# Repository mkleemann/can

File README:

AVR module: CAN - using MCP2515 and MCP2551
================================================================================

A submodule used in other projects. Currently cmake is used to build a library
of the module. The path structure within the project should be as follows.
The includes are looked for in the subdirectory "config", "spi" and "util" at
the same level as the module.

Environment:
------------

<some project path>
:
|
+- config
|  |
|  +- can_config_mcp2515.c
|  +- can_config_mcp2515.h
|  +- spi_config.h
|
+- can
|  |
|  +- <submodule sources>
|
+- spi
|  |
|  +- <submodule sources>
|
+- util
   |
   +- <submodule util files>

Use the following git commands to get the submodule:

# to get the submodule
git submodule add git@github.com:mkleemann/can.git <path/to/can/module>
# commit the submodule to your repository
git commit

# update your submodule, when needs be
git submodule update

To use the submodule, you may make use of the cmake-avr toolchain. The
project has to define the include search path at the parent directory
of the module.

Have fun!

M.

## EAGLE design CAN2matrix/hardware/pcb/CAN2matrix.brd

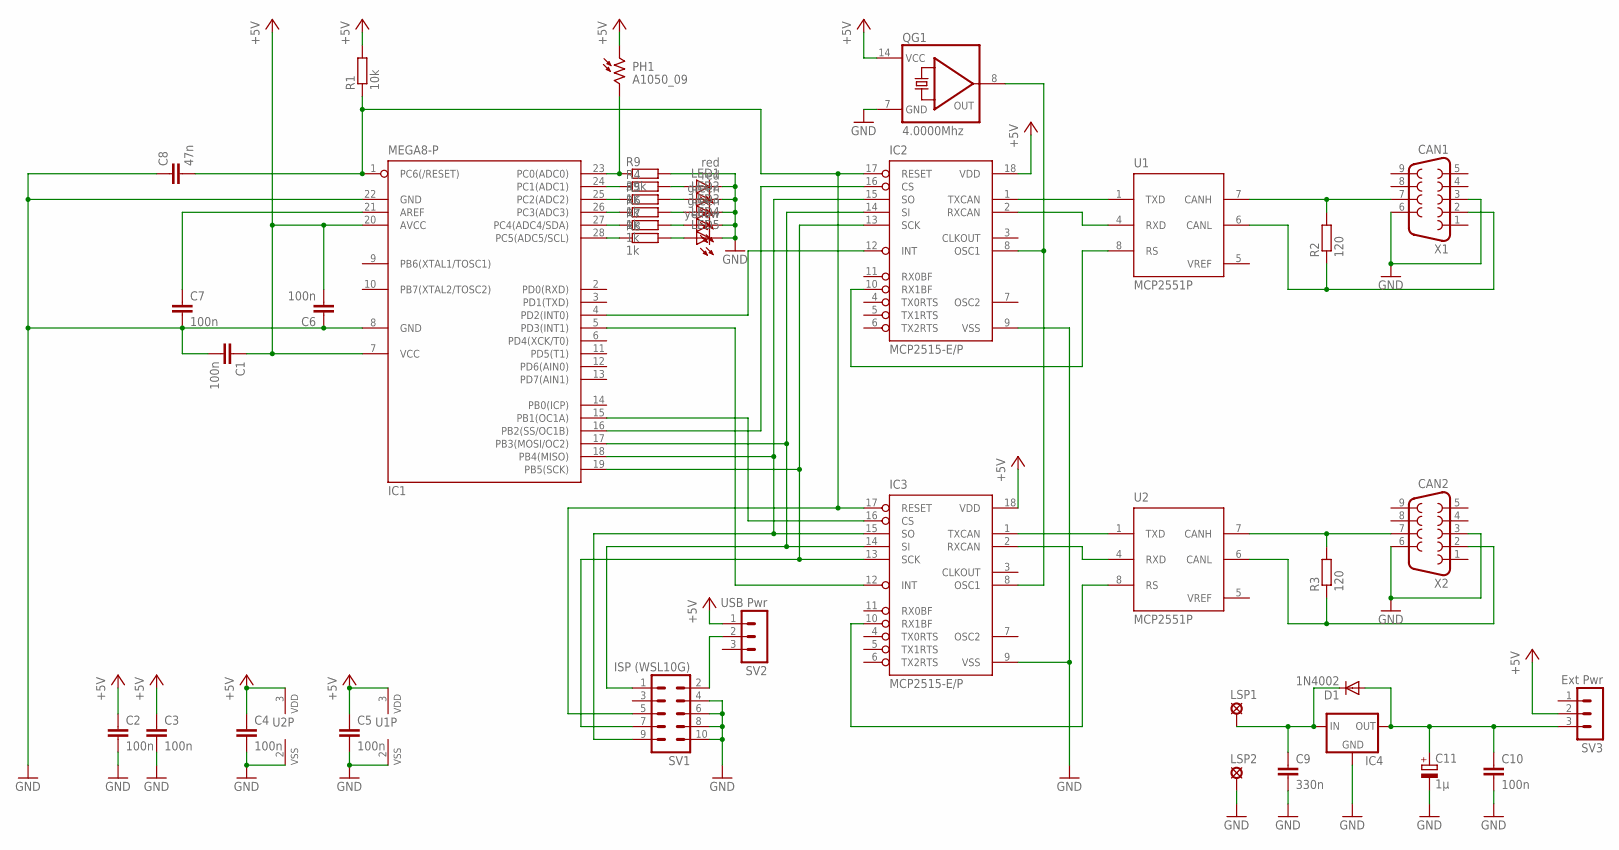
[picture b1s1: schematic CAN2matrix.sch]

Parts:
C1, C2, C3, C4, C5, C6, C7, C10: 100n; C050-025X075
C8: 47n; C050-025X075
C9: 330n; C050-025X075
C11: 1µ; E2,5-7
D1: 1N4002; DO41-10
IC1: MEGA8-P; DIL28-3
IC2, IC3: MCP2515-E/P; DIL18
IC4: 78LXX
LED1, LED2: red; LED3MM
LED3, LED4: green; LED3MM
LED5: yellow; LED3MM
LSP1: +12V; SE14
LSP2: SE14
PH1: A1050_09; T0-46-A10XX
QG1: 4.0000Mhz; DIL14S
R1: 10k; 0207/2V
R2, R3: 120; 0207/2V
R4, R5, R6, R7, R8: 1k; 0207/10
R9: 39k; 0204/7
SV1: ISP (WSL10G); ML10
SV2: USB Pwr; MA03-1
SV3: Ext Pwr; MA03-1
U1, U2: MCP2551P; DIL8
X1: CAN1; F09HP
X2: CAN2; F09HP

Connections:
+5V: C1.1, C2.1, C3.1, C4.1, C5.1, C6.2, IC1.7 (VCC), IC1.20 (AVCC), IC2.18 (VDD), IC3.18 (VDD), PH1.1, QG1.14 (VCC), R1.2, SV2.1, SV3.2, U1.3 (VDD), U2.3 (VDD)
+12V: C9.1, D1.C, IC4.IN, LSP1.MP
GND: C1.2, C2.2, C3.2, C4.2, C5.2, C6.1, C7.2, C8.1, C9.2, C10.2, C11.-, IC1.8 (GND), IC1.22 (GND), IC2.9 (VSS), IC3.9 (VSS), IC4.GND, LED1.K (C), LED2.K (C), LED3.K (C), LED4.K (C), LED5.K (C), LSP2.MP, QG1.7 (GND), R9.2, SV1.4, SV1.6, SV1.8, SV1.10, U1.2 (VSS), U2.2 (VSS), X1.3, X1.6, X2.3, X2.6
unnamed: IC1.18 (PB4(MISO)), IC2.15 (SO), IC3.15 (SO), SV1.9
unnamed: IC1.17 (PB3(MOSI/OC2)), IC2.14 (SI), IC3.14 (SI), SV1.1
unnamed: IC1.19 (PB5(SCK)), IC2.13 (SCK), IC3.13 (SCK), SV1.7
unnamed: R2.2, U1.7 (CANH), X1.7
unnamed: R3.2, U2.7 (CANH), X2.7
unnamed: R3.1, U2.6 (CANL), X2.2
unnamed: IC3.10 (RX1BF), U2.8 (RS)
unnamed: C7.1, IC1.21 (AREF)
unnamed: C8.2, IC1.1 (PC6(/RESET)), IC2.17 (RESET), IC3.17 (RESET), R1.1, SV1.5
unnamed: IC2.1 (TXCAN), U1.1 (TXD)
unnamed: IC2.2 (RXCAN), U1.4 (RXD)
unnamed: IC3.1 (TXCAN), U2.1 (TXD)
unnamed: IC3.2 (RXCAN), U2.4 (RXD)
unnamed: IC1.16 (PB2(SS/OC1B)), IC2.16 (CS)
unnamed: IC1.15 (PB1(OC1A)), IC3.16 (CS)
unnamed: IC1.4 (PD2(INT0)), IC2.12 (INT)
unnamed: IC1.5 (PD3(INT1)), IC3.12 (INT)
unnamed: IC2.8 (OSC1), IC3.8 (OSC1), QG1.8 (OUT)
unnamed: IC2.10 (RX1BF), U1.8 (RS)
unnamed: R2.1, U1.6 (CANL), X1.2
unnamed: SV1.2, SV2.2
unnamed: IC1.24 (PC1(ADC1)), R4.1
unnamed: IC1.25 (PC2(ADC2)), R5.1
unnamed: IC1.26 (PC3(ADC3)), R6.1
unnamed: IC1.27 (PC4(ADC4/SDA)), R7.1
unnamed: IC1.28 (PC5(ADC5/SCL)), R8.1
unnamed: LED1.A, R4.2
unnamed: LED2.A, R5.2
unnamed: LED3.A, R6.2
unnamed: LED4.A, R7.2
unnamed: LED5.A, R8.2
unnamed: IC1.23 (PC0(ADC0)), PH1.2, R9.1
unnamed: C10.1, C11.+, D1.A, IC4.OUT, SV3.3
VREF: U1.5 (VREF), U2.5 (VREF)

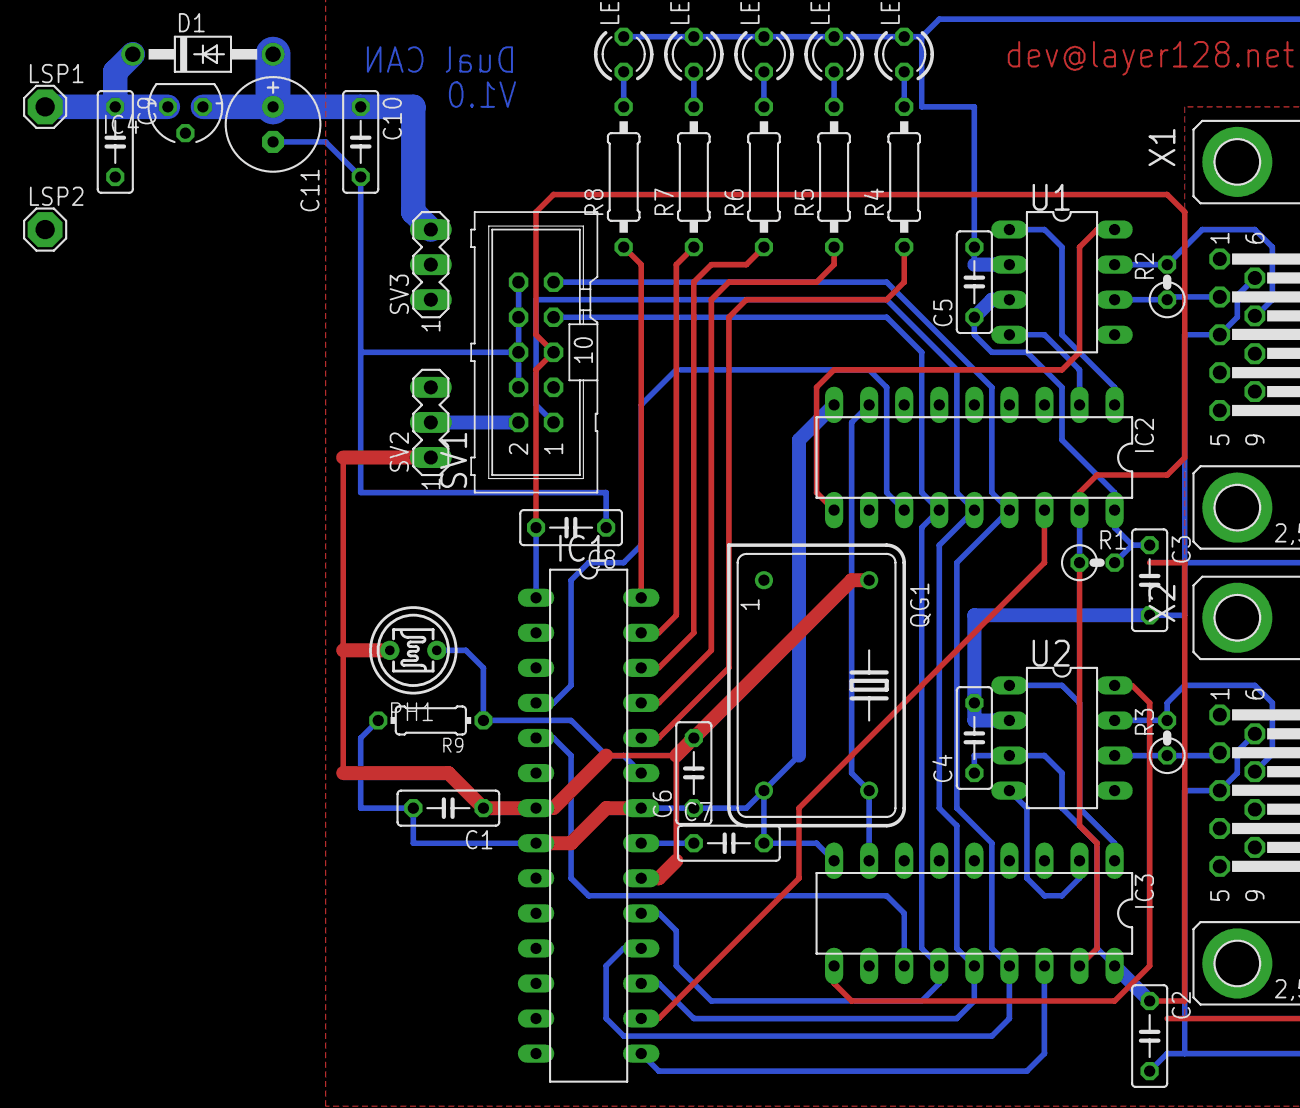
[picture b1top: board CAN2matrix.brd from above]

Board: 2 copper layers, 41 parts (0 on the bottom side), 37 nets.

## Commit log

2011-12-02 initial version
2011-12-02 add code to spi and uart, remove eeprom, change Release options
2011-12-04 Defintion of utilities for PORT/PIN usage and debug prints.
2011-12-06 implement first version of led control
2011-12-06 make it compilable
2011-12-13 intermediate stage with tested LEDs on ATmega8
2011-12-13 remove file can.h
2011-12-16 put #define of number of leds to enum
2011-12-16 last changes to UART for testing with MAX232
2011-12-16 change documentation wthin file
2011-12-16 intermediate stage for CAN implementation - compiles; not yet tested
2011-12-17 add F_CPU and MCP_CLOCK to compiler symbols to avoid delay.h warnings
2011-12-17 CAN init w/o filters; compiles; not tested
2011-12-17 rename can_write to can_send
2011-12-17 setup SPI port pins
2011-12-17 intermediate stage for CAN cluster; acknowledgements; compiles; not tested
2011-12-19 intermediate stage for CAN cluster - send/receive; compiles; not tested
2011-12-19 changed AVRStudio project files
2011-12-19 add modes of operation to MCP2515 control; compiles; not tested
2011-12-20 guard SPI pins and beautify code a little
2011-12-21 major bugs in macros fixed
2011-12-21 use different macros and pin definitions to avoid bugs
2011-12-21 intermediate stage with new approach to CS/INT pins; partly simulated; compiles; not tested on HW
2011-12-21 testing with one CAN chip attached; intermediate stage
2011-12-21 update AVRStudio 5 project files
2011-12-21 update AVRStudio 5 project files - change back to atmega8 (from 16)
2011-12-26 add filters to CAN init; some changes to can_get_message (skip ext ids); minor changes; first tested with live CAN - OK
2011-12-26 minor changes to SPI files
2011-12-26 bug fixed/newly added utilities
2011-12-26 test program with one attached MCP2515; working with external CAN adapter
2011-12-26 changed project files for AVRStudio 5
2011-12-27 add README file to project
2011-12-27 add AVRStudio 5 note to README
2011-12-27 add LICENSE (beerware) and update README
2011-12-27 add ANY BEVERAGE-WARE license to files
2011-12-27 add hardware/schematics for documentation; schematics also as EAGLE V6.0 file
2011-12-27 move sleep/wakeup functions to can_sleep_mcp2515.c
2011-12-27 enable Wake On CAN interrupt in configuration; introduce different wake up scenarios for sleep mode; compiles; not tested
2011-12-27 update README (typo)
2011-12-27 update schematics to provide possibility to disconnect ISP power supply from board
2011-12-27 move clear filter function to can_filter_mcp2515.c
2011-12-29 add filter setup functions (no implementation); cleanup a little
2011-12-29 implement Timer0 simple use for overflow interrupt; Timer1/2 still not implemented
2011-12-29 use Timer0 to trigger simple CAN msg every 250ms (approx.); verified and tested
2011-12-29 update AVRStudio 5 files
2011-12-29 add start/stop functions for Timer0; init stops timer
2011-12-29 set RX1BF as digital output to use as sleep mode indicator for MCP2551
2011-12-29 update AVRStudio 5 file
2011-12-29 add sleep/wakeup functions and ISR to main(); tested but does not yet enter sleep mode yet
2011-12-31 Only put MCP2551 to sleep, when waking MCP2515 up manually. Otherwise the wake up by CAN does not work.
2012-01-01 add timer1/2 functions; partly tested; save workspace only
2012-01-01 reworked main program; partly tested (bussleep timer not yet working); save workspace only
2012-01-02 timer initialization errors removed
2012-01-02 implement restart timer 1/2 functionality
2012-01-02 correct comment
2012-01-02 use Timer1 for CAN bus sleep detection - 15s timer value set
2012-01-03 prepare for matrix implementation; add matrix.c to project
2012-01-03 first introduction of CAN ids; save intermediate stage
2012-01-03 matrix compiles now; does nothing yet
2012-01-03 add minimal navigation signals IGN, Wheel Count and Reverse Gear to matrix
2012-01-03 add CAN2 signals for minimal navigation; correct CAN ids
2012-01-03 bus sleep detection tested & working; IGN status and wheel count messages corrected; IGN tested with target radio - OK
2012-01-03 working minimal matrix
2012-01-04 add new led configuration
2012-01-04 first test version with 2 CAN busses; compiles; partly tested
2012-01-04 add .gitignore to file list in preparation to makefile creation
2012-01-04 remove warnings (no prototype) and errors (type conflict due to copy&paste)
2012-01-04 add makefile for WINAVR or AVRStudio 5 toolchain from command line - not finetuned yet
2012-01-04 rework pin definitions for leds to avoid compiler warning
2012-01-04 add AVR sleep mode (power down); untested
2012-01-04 remove CAN2matrix.avrsuo workspace file
2012-01-04 make CAN trigger more robust
2012-01-05 add -pedantic to gcc flags
2012-01-05 remove German comments
2012-01-05 use all prescaler bits to stop timers - just in case
2012-01-05 set -pedantic for AVRStudio 5 too
2012-01-05 remove warning 'type of bit field is a gcc extension' by using 'unsigned int' instead of 'uint8_t'
2012-01-06 remove comments and set commas in struct
2012-01-07 tweak timer config a little
2012-01-07 move pins by 1 for leds
2012-01-07 tested with matrix and real radio; wakeup from sleep not working yet - so removed by now
2012-01-07 add led_all_off() for AVR power down modes
2012-01-07 some changes for power down testing
2012-01-09 change interrupt trigger to 'any chang e of level'
2012-01-15 add possibility to use CLKOUT of master CAN to drive slave CAN or others
2012-01-15 update README and save current state of testing wakeup via CAN
2012-01-25 add led_all_on()
2012-01-25 add PIN_SET_PULLUP define
2012-01-25 adjust comment
2012-01-27 set optimization for simulator to -Os for debugging
2012-01-27 code cleanup - use PIN_SET_PULLUP() to init interrupt pins now
2012-01-27 reworked main: add FSM, add simulation possibility w/o CAN, code cleanup
2012-01-27 some minor changes for interrupt handling and signalling
2012-01-27 Complete restructure of the state engine. Refactoring of the very big main method.
2012-01-27 compiles now
2012-01-27 set wakeup interrupt trigger to low level
2012-01-29 redo restartTimerX and add set TimerXCount; X = 1,2
2012-01-29 add single CAN for testing; use simulation mode to test wakeup
2012-01-29 remove debugging artefact (back to 100kbps)
2012-01-31 now wakeup works also with power down mode on atmega8
2012-01-31 wakeup via CAN with one CAN bus attached works now too
2012-01-31 current state of affairs
2012-01-31 typos and beautifying
2012-02-01 refacturing run() and some beautifying; tested in simulation ok
2012-02-01 beautifying code and remove redundant comments
2012-02-02 clean up SPI configuration and header
2012-02-02 clean up code and change configuration w/o the need to update leds.c when using more or less port pins/leds
2012-02-02 clean up code to put only configuration definitions to config file
2012-02-04 add expand macros for PIN, PORT and DDR
2012-02-04 add bargraph files and init() to project; configuration might currently not usable with LED definitions
2012-02-04 first version of bargraph; not yet fully tested
2012-02-07 tested standard and inverted bar
2012-02-07 correct comments
2012-02-08 correct description of inverted mode and add reverse mode
2012-02-08 add possibility of an pin offset to bargraph
2012-02-09 add chip select functionality; configuration changed to current test environment
2012-02-24 change makefile to AVRStudio 5 environment; no avrdude support currently; needs to set environment variable AVR_APP_PATH to install path of AVR toolchain within AVRStudio
2012-02-24 remove single CAN setup
2012-02-24 add ADC component template to dim radio dynamically
2012-02-25 add first adc configuration (not tested yet) and enable/disable functions
2012-02-27 complete adc get value as 'one-shot conversion with wait until ready'; not tested in hardware yet
2012-02-27 add adc to main program for testing
2012-02-29 move CAN message setup to matrix; add radio dim value message correctly
2012-02-29 optimize ADC so it can be used with (upper) 8bit resolution
2012-02-29 use dim value with ADC 8bit resolution
2012-02-29 add dimming bit definitions and threshold
2012-03-01 set adc input pin
2012-03-01 fix typo to correct shift operation for ADLAR in 8bit resolution mode
2012-03-02 code/comment cleanup for better overview
2012-03-02 cleanup for better overview
2012-03-02 comment cleanup for better overview
2012-03-06 change contact address in license information
2012-03-06 change back accidentally set SPI prescaler
2012-03-06 update .gitignore for AVRStudio 5.1 file naming
2012-03-06 add AVRStudio 5.1 solution files; not remove 5.0 files for now
2012-03-06 rework dimming with averaging measured values; add single CAN testing
2012-03-06 rework single CAN testing with dimming/adc; remove typos in function names
2012-03-07 make dim level a floating average to have a smoother transition
2012-03-07 insert hysteresis for day/night mode switch with upper limit default value
2012-03-07 fix typo
2012-03-08 add -save-temps to makefile and extend cleanup section
2012-03-08 add -Wall and -pedantic-errors to Release build of AVRStudio
2012-03-08 add LEDs to schematics
2012-03-08 add light dependent resistor for dimming; update schematics and image
2012-03-08 add first pcb (placement only) to hardware (Eagle 6.1.0)
2012-03-10 V1.0 of PCB and adjusted schematics
2012-03-11 add non-USB power supply to schematics and PCB; export images
2012-03-11 remove orphans from polygones
2012-03-11 remove erroneous connection between GND and power supply wire at C10
2012-03-13 rework top layer to avoid shortcuts with Sub-D connector; solve overlapping error with connector pad
2012-03-14 add solder stop masks fro top/bottom
2012-03-14 shorten reset wire in top layer
2013-03-12 prepare to use submodules
    - prepare for use of submodules and extract configuration
    - fix include paths
    - change doxygen files for use in submodule
    - adjust doxygen reference
    - adjust gitignore
    - adjust makefiles
2013-04-20 add example configuration
    Taken over from CAN2matrix, but used as examples here. The files
    can be adapted to meet your needs. Take a look at the enumerations and
    selection macros. The dependencies need to be considered setting the
    can module up.
2013-04-29 add further documentation
    - rework examples for unique look&feel
    - add README
    - correct references to files
2014-01-01 add CMakeLists.txt for build as simple library
    - needs cmake-avr toolchain
2014-01-13 cleanup includes and update README
    - remove ../ in include paths
    - update README in regards of cmake
2014-01-13 remove typos in README
2014-01-17 cleanup includes
    - util.h now included via project configuration, since it
    is necessary nevertheless
    - cleanup include tree
2014-02-22 correct documentation
    - examples are most likely not taken into the documentation, so
    use the real configuration files instead
    - page_spi must be included first with doxygen
